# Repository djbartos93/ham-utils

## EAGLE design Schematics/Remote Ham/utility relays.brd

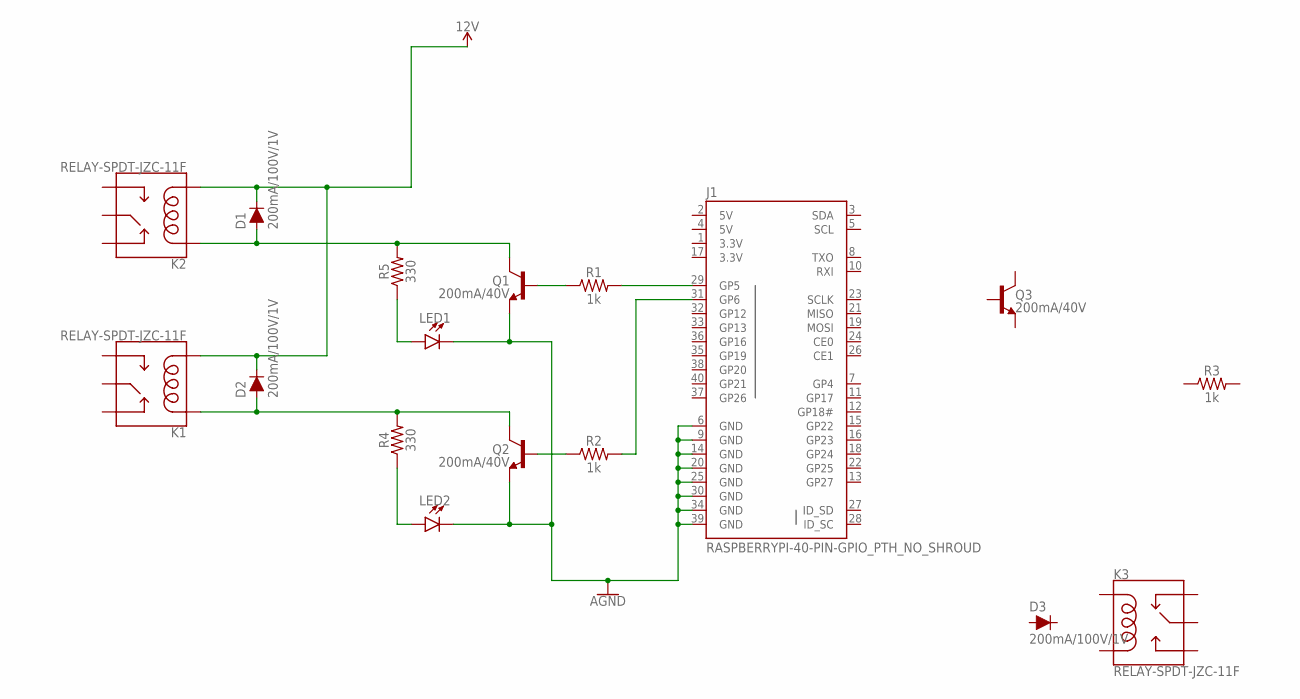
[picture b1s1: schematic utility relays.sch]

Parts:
D1, D2, D3: 200mA/100V/1V; DIODE-1N4148
J1: RASPBERRYPI-40-PIN-GPIO_PTH_NO_SHROUD; 2X20
K1, K2, K3: RELAY-SPDT-JZC-11F; RELAY-JZC
LED1, LED2: LED3MM; LED_3MM
Q1, Q2, Q3: 200mA/40V; TO-92
R1, R2, R3: 1k; AXIAL-0.3
R4, R5: 330; AXIAL-0.3

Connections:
3.3V: J1.1 (3.3V), J1.17 (3.3V)
5V: J1.2 (5V), J1.4 (5V)
12V: D1.C, D2.C, K1.1 (COIL2), K2.1 (COIL2)
AGND: J1.6 (GND), J1.9 (GND), J1.14 (GND), J1.20 (GND), J1.25 (GND), J1.30 (GND), J1.34 (GND), J1.39 (GND), LED1.K (C), LED2.K (C), Q1.1 (E), Q2.1 (E)
unnamed: D1.A, K2.5 (COIL1), Q1.3 (C), R5.P$2 (2)
unnamed: D2.A, K1.5 (COIL1), Q2.3 (C), R4.P$2 (2)
unnamed: Q2.2 (B), R2.P$1 (1)
unnamed: Q1.2 (B), R1.P$1 (1)
unnamed: LED2.A, R4.P$1 (1)
unnamed: LED1.A, R5.P$1 (1)
unnamed: J1.29 (GP5), R1.P$2 (2)
unnamed: J1.31 (GP6), R2.P$2 (2)

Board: 2 copper layers, 17 parts (0 on the bottom side), 12 nets, no tracks yet.

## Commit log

2018-12-13 Simple USB To serial for Teensy 2.0
2018-12-16 adding utility relays

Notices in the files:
parts and their libraries:
SparkFun-DiscreteSemi: Licensing: Creative Commons ShareAlike 4.0 International - https://creativecommons.org/licenses/by-sa/4.0
